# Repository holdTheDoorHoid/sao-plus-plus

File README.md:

# SAO++

Classic Simple Add-Ons, rebuilt for today's badges and for real production runs, plus a growing set of new ones.

The repo holds two kinds of board, kept in separate folders:

- **Ports** (`boards/`): other makers' SAOs, rebuilt to the SAO++ standard with credit to the original maker.
- **SAO++ Originals** (`originals/`): LSOH's own designs, made for SAO++ from scratch.

SAO++ takes older SAOs (the little art boards that plug into conference badges), ports them to the **SAO v1.69bis** 6-pin standard, adds small improvements where they make sense, and publishes them openly. Every board shares the same connector, power switch, battery holder, and LED family, so they can be built side by side on the same reels and the same assembly setup.

## What every SAO++ board has

- **6-pin SAO v1.69bis connector**, surface-mount and shrouded, on the back. Nothing pokes through the art side.
- **SAO / OFF / BATTERY switch**: runs from the badge or from its own CR2032. It is wired so the badge can never charge the coin cell.
- **CR2032 coin cell**: several days of daytime wear on a simple LED board.
- **Boards that need a chip** use a Seeed Studio XIAO ESP32 module instead of a coin cell: the same switch chooses between badge power and the module's own (USB-C or a LiPo).
- **LEDs on the back**: side-firing ones that light the art from the edges, or reverse-mount ones that shine through the board.
- **All parts on the back**; the front is pure art.

The full rules are in [docs/standard.md](docs/standard.md), and the shared parts with live prices are in [docs/parts.md](docs/parts.md).

## Layout

```
boards/<slug>/        one folder per PORT of another maker's SAO
originals/<slug>/     one folder per SAO++ ORIGINAL (LSOH's own design); same layout as a port
  board.yml           provenance, license, permission, features, shared parts used
  README.md           credit to the original maker, what changed, build notes
  hardware/           KiCad 10 project
  art/                source artwork
  production/         Gerbers, drill, BOM and placement files for one board and for a panel
  firmware/           only for boards with a microcontroller
boards/_template/     copy this to start a new board
lib/                  shared KiCad symbols, footprints, 3D models, power block, starter project
docs/                 house standard, approved parts, porting and permission guide
tools/                check_boards.py (paperwork check, runs on every push), gen_footprints.py, saopp_symbols.py,
                      gen_schematic.py, extract_outline.py, saopp_board.py (helpers for each board's build script), panelize.py, export_fab.py
```

## Ports

Other makers' SAOs, rebuilt. Credit and permission status are in each board's README.

| Board | Original maker | Status |
|---|---|---|
| [Fat Pika](boards/fat-pika/) | TwinkleTwinkie (DEF CON 26, 2018) | Designed and rule-checked, not yet built. **Permission pending: not open-licensed**, see the board README |
| [Mad Cat](boards/mad-cat/) | TwinkleTwinkie (DEF CON 26, 2018) | Designed and rule-checked, not yet built. **Permission pending: not open-licensed**, see the board README |
| [Big Green](boards/big-green/) | TwinkleTwinkie (DEF CON 26, 2018) | Designed and rule-checked, not yet built. **Permission pending: not open-licensed**, see the board README |
| [La Bomba](boards/la-bomba/) | TwinkleTwinkie (DEF CON 26, 2018) | Designed and rule-checked, not yet built. **Permission pending: not open-licensed**, see the board README |
| [Nibbler](boards/nibbler/) | TwinkleTwinkie (DEF CON 26, 2018) | Designed and rule-checked, not yet built. **Permission pending: not open-licensed**, see the board README |
| [RBG](boards/rbg/) | lemons4all (DEF CON 26, 2018) | Designed and rule-checked, not yet built. **Permission pending: not open-licensed**, see the board README |
| [Frida](boards/frida/) | lemons4all (DEF CON 26, 2018) | Designed and rule-checked, not yet built. **Permission pending: not open-licensed**, see the board README |
| [Oh My Glob (LSP)](boards/lumpy/) | lemons4all (DEF CON 26, 2018) | Designed and rule-checked, not yet built; the tightest fit of the set (see its README). **Permission pending: not open-licensed** |
| [Hack-Man](boards/hack-man/) | InstantArcade (Bob), 2024 | Recreated from the maker's pictures (no files were published), rule-checked, not yet built. Seeed XIAO ESP32 controller, new Rust firmware. **Permission pending: not open-licensed**, see the board README |
| [Han SAOlo](boards/han-saolo/) | davedarko (2024) | Designed and rule-checked, not yet built. Short life and weak green/blue on a coin cell (calculated). **Permission pending: not open-licensed**, see the board README |
| [Knight Rider (K.I.T.T.)](boards/knight-rider/) | davedarko (2017) | Designed and rule-checked, not yet built. No firmware yet. **Permission pending: not open-licensed**, see the board README |
| [Soot Sprite](boards/soot-sprite/) | davedarko (2026) | Designed and rule-checked, not yet built. **Permission pending: not open-licensed**, see the board README |
| [COVID-19 Test](boards/covid-test/) | davedarko (2022) | Designed and rule-checked, not yet built. **Permission pending: not open-licensed**, see the board README |
| [Penghito Poco](boards/penghito-poco/) | davedarko (year not recorded) | Designed and rule-checked, not yet built. **Permission pending: not open-licensed**, see the board README |
| [Mysterio](boards/mysterio/) | davedarko (2025) | Designed and rule-checked, not yet built. Seeed XIAO ESP32 controller, new Rust firmware (never run on hardware). **Permission pending: not open-licensed**, see the board README |
| [Do Or Donut](boards/do-or-donut/) | davedarko (2019) | Designed and rule-checked, not yet built. Seeed XIAO ESP32 controller, new Rust firmware (never run on hardware). **Four-layer board.** **Permission pending: not open-licensed**, see the board README |
| [Vendetta](boards/vendetta/) | davedarko (2022) | Designed and rule-checked, not yet built. Scaled up 1.23x. **Permission pending: not open-licensed**, see the board README |
| [Hello My Name Is](boards/hello-my-name-is/) | davedarko (2024) | Designed and rule-checked, not yet built. Scaled up 1.1x. **Permission pending: not open-licensed**, see the board README |
| [LECCO postcard](boards/lecco/) | davedarko (2026) | Designed and rule-checked, not yet built. Scaled up 1.2x; badge power only (no cell or switch). **Permission pending: not open-licensed**, see the board README |
| [Sloth](boards/sloth/) | davedarko (2017) | Was a pin; now an SAO. Designed and rule-checked, not yet built. Scaled up 1.3x. No firmware yet. **Permission pending: not open-licensed**, see the board README |
| [Flux Capacitor](boards/flux-capacitor/) | davedarko (2017) | Was a pin; now an SAO. Designed and rule-checked, not yet built. Scaled up 1.35x. No firmware yet. **Permission pending: not open-licensed**, see the board README |
| [Retro Spacehuhn](boards/spacehuhn/) | davedarko (year not recorded) | Was a pin; now an SAO. Designed and rule-checked, not yet built. The chicken logo is Spacehuhn's. **Permission pending: not open-licensed**, see the board README |
| [Mr. Robot](boards/mr-robot/) | davedarko (2019) | Designed and rule-checked, not yet built. Scaled up 1.1x. Seeed XIAO ESP32 controller, new sounder driver, new Rust firmware (never run on hardware). **Permission pending: not open-licensed**, see the board README |

## SAO++ Originals

LSOH's own designs, under the SAO++ licences. None is built yet; the first shortlist of ten
cybersecurity-themed art boards is in [originals/README.md](originals/README.md).

## Adding a board

Read [docs/porting-guide.md](docs/porting-guide.md). In short: confirm the license or get the maker's permission **first**, copy `boards/_template` (into `originals/<slug>/` for an LSOH design, with `permission: own`), start from `lib/template`, and run `python3 tools/check_boards.py`.

## License

- Hardware designs: [CERN-OHL-S-2.0](LICENSE). Anyone can build and sell these; changes you distribute must stay open.
- Artwork: [CC-BY-SA-4.0](LICENSE-ART).
- **These licenses cover SAO++'s own work only**, which includes every board in `originals/` in full. A board marked "permission pending" in its README is not open-licensed: its original design and art stay with the original maker.
- Boards ported from other makers keep their credit, and their original license terms are recorded in each `board.yml`. Where a board's original license differs, its README says so and it takes precedence for that board.

Original designs remain credited to their makers. If you made one of these boards and want it changed or removed, open an issue.

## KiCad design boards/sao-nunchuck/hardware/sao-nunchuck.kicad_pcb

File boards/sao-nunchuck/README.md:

# SAO Nunchuck — SAO++ edition

Originally the **SAO Nunchuck** (hardware V1.0, 2024) by **Andy and Jared Geppert** (ageppert, www.MachineIdeas.com): https://github.com/ageppert/SAO_Nunchuck (project page: https://hackaday.io/project/198000-sao-nunchuck)

**License:** the original is MIT-licensed, "Copyright (c) 2024 Andrew Geppert" ([original/LICENSE.md](original/LICENSE.md)). The license sits at the top of the maker's repository and no file inside carries a different notice, so it covers the board design as well as the demo code. That notice must stay with any copy.

> **The names and shapes are Nintendo's.** "Wii" and "Nunchuk" are Nintendo trademarks. The board says "SAO NUNCHUCK" on the back (the maker's spelling) and shows the outline of a Wii Remote and a Nunchuk controller on the front, joined by a chain like a pair of nunchaku. There is no Nintendo logo on it. The maker's MIT license covers his drawing; it cannot give anyone rights in Nintendo's names or product shapes. If boards are sold, describe them as "for use with" the controller, never as a Nintendo product. The owner should decide whether that is enough (see "Decisions for the owner").

## What the original actually is

Read from the maker's files (the survey guessed "pass-through, hardly any art"; the first half is right, the second is not):

- **A plug-in adaptor with no parts that do anything.** A Nunchuck controller talks I2C (the same two-wire bus an SAO port has) and runs on 3.3 V. The board joins the badge's 3.3 V, ground, SDA and SCL straight to the controller's plug. No chip, no LED, no resistor, no pull-ups. The badge's own program reads the joystick, two buttons and tilt sensor at I2C address 0x52 (printed on the back).
- **The board is the socket.** There is no bought connector for the controller. The top edge has a notch with a 6.3 mm wide tongue in it, carrying five gold fingers (three on the back, two on the front). The controller's plug slides over the tongue; the notch is shaped to take the plug's body and latches. One of the six plug contacts ("device detect") lands on a finger that is not connected to anything; the sixth has no finger.
- **Two Qwiic sockets** (small 4-pin JST SH connectors, the SparkFun / Adafruit plug-and-play I2C standard) on the back near the top corners, wired to the same four lines, so the board can also join a Nunchuck to a Qwiic gadget, or chain other I2C boards off the badge.
- **The SAO header** was a through-hole 2×3 at the bottom, with six extra gold fingers on the bottom edge so a right-angle socket could be soldered on instead (that is what the maker's photo shows).
- **It does have art:** a Wii Remote and a Nunchuck as a pair of nunchaku, in bare gold copper on a black board, 38.1 × 50.8 mm.
- **Demo code** (`original/Firmware/`, Arduino, for an RP2040 board) shows how to read the controller. It is the badge's job, not the add-on's: there is nothing on this board to program.

## What SAO++ makes of it

The same adaptor, with the house connector on the back. **One part to buy and place.**

| | Original (V1.0) | SAO++ rev A |
|---|---|---|
| SAO connector | Through-hole 2×3 at the bottom (six holes through the front), plus six edge fingers | 6-pin SAO v1.69bis shrouded, keyed SMD connector on the back, in the same three columns, key slot up. Nothing shows on the front |
| Power | Badge 3.3 V only | **Badge 3.3 V only** (no coin cell, no switch: see below). "BADGE POWER ONLY" is printed on the back |
| Nunchuck plug | Five gold fingers on a tongue in the top notch | **Unchanged**: same notch, same tongue, same fingers, same wiring |
| Qwiic sockets | Two JST SH 4-pin sockets fitted | **Pads only, not fitted.** The pads and wiring are all there; solder a socket on by hand if you want one |
| Front art | — | Unchanged, apart from the old header's six holes and three bottom fingers, which are gone |
| Back | — | Title, I2C address, makers' credit and logo, "2024" and "V1.0" untouched. "Manufactured by PCBX.COM" removed (it would not be true of these boards). Added: "SAO++ rA   BADGE POWER ONLY", a pin-1 mark, and a ground copper fill under the mask |

**How to use it:** plug the board into a badge's SAO port, then push a Nunchuck plug onto the tongue at the top until it clicks. The badge needs a program that reads a Nunchuck (libraries are linked in the maker's README).

## Why there is no coin cell and no switch (a recorded exception to the house standard)

Every other SAO++ board so far has the CR2032 clip and the SAO / OFF / BAT switch. This one does not, on purpose:

- **Nothing on it lights up or runs on its own.** A Nunchuck with nobody reading it does nothing, and the only thing that can read it is the badge. A cell would power a controller that is not being listened to.
- **A cell here would be the risky case in the standard.** Section 3 warns that when the badge's I2C lines are connected to something powered by the cell, a little current can leak from the badge into the cell. This board is *only* I2C lines. Fitting a cell would mean adding the protective diode as well, three parts in all, to guard a feature nobody can use.
- **It keeps the board to one shared part.**

So SAO pin 1 (3.3 V) goes straight to the plug and the Qwiic pads, as the maker drew it, instead of through a switch (the standard's pin-1 rule assumes a switch exists). With no cell on the board there is nothing to back-feed.

## Other compromises, each one deliberate

- **Two gold fingers are on the front.** The house rule is "front = art only". A Nunchuck plug has contacts on both faces of the tongue, so two fingers must be on the front. They are the maker's and are part of the look.
- **The maker's tracks on the front stay.** Five thin tracks cross the front just above the chain (under the mask, faintly visible) with 16 small vias. They are his way of getting four lines to both Qwiic positions. They were left exactly as drawn rather than re-routed.
- **Connector at the bottom, not the middle.** The standard prefers the connector near the board's centre of weight. The middle of the back is the maker's title and credit, and the original header was at the bottom too. The connector's pads end 3.4 mm inside the bottom edge (rule: 3 mm). The controller's cable will pull on the top of the board while the connector holds the bottom: see the checklist.
- **Qwiic sockets not fitted.** The JST SH socket is not on the shared parts list, and fitting it would add a reel that only this board uses. The pads cost nothing. The maker's files name the part as JST **SM04B-SRSS-TB** (his file also carries LCSC C160404 and a Digi-Key number; none of these was re-checked here).
- **"V1.0" and "2024" stay** on the back as the maker's version of the design, next to the new "SAO++ rA".
- **The title is slightly wider than the board.** The maker's "SAO NUNCHUCK" lettering runs 0.2–0.4 mm past both side edges, so the tips of the S and K are trimmed, exactly as on his boards. Left alone.
- **Ground copper fill on the back** is new (the standard asks for copper round the connector to stiffen the joint). It stops 0.55 mm from the edge and stays off the tongue and out of the notch.

## Things to check on the first prototype

1. **Plug fit.** Push a real Nunchuck plug on. It should slide over the tongue, click, and not wobble. The tongue, notch and fingers are the maker's, unchanged, and he built and used his, but **the board must be 1.6 mm thick** for the plug's springs to grip.
2. **Does it work.** On a badge with a Nunchuck program (or the maker's Arduino demo on an RP2040 board), check the joystick and buttons read correctly. Check with a genuine controller and, if you have one, a clone: some clones need pull-up resistors that genuine ones have built in, and this board, like the original, has none (the badge is expected to provide them).
3. **Pin 1 position.** The connector keeps 3.3 V in the same corner as every other SAO++ board. Confirm against a v1.69bis badge before a production run. A wrong guess here would put 3.3 V and ground the wrong way round on the controller.
4. **Current.** Measure what the controller draws from the badge. It was not measured here; the house budget is 50 mA.
5. **Cable pull.** With the controller plugged in and hanging or being used, check the SMD connector's solder joints are not being levered. If they are, the fix is the connector higher up the board, which means moving the maker's credit block (owner's call).
6. **Clearance behind the board.** The plug's body is thicker than the board and sticks out behind it at the top. The SAO connector holds the board about 9 mm off the badge, which should be enough; check on a real badge.
7. **Gold finger wear.** ENIG gold is thin. It is fine for occasional plugging; if a board is going to be plugged hundreds of times, ask the fab about hard gold.

## Files

- `hardware/sao-nunchuck.kicad_pro` — KiCad 10 project (schematic + board). ERC: 0 issues. DRC: 0 errors, 0 unconnected, schematic matches board. 2 warnings remain: the maker's logo library is not installed (the logo itself is in the board), and the maker's title lettering touches the board edge (see above).
- `hardware/circuit.json` — the circuit as data; `tools/gen_schematic.py sao-nunchuck` and `hardware/build_board.py` both read it. `hardware/fix_schematic.py` then marks the fingers and the Qwiic pads "not in BOM".
- `hardware/build_board.py` — rebuilds the board from `original/` plus the SAO++ changes; every decision is in there with a comment. It also re-applies the project's rule settings (the maker's 6 mil spacing between his tracks and vias is kept as the board's minimum).
- `hardware/sao-nunchuck.kicad_dru` — one extra rule: the plug fingers may run to within 0.1 mm of the tongue's tip (the maker's are 0.14 and 0.19 mm).
- `hardware/parts_local.py`, `hardware/sao-nunchuck-local.pretty/`, `hardware/make_local_footprints.py` — the two footprints kept from the maker (plug fingers; Qwiic pads), lifted out of his board file.
- `hardware/outline.json` — the maker's outline as one polygon.
- `production/` — everything a board house needs, for one board (`single/`) and a 2×2 panel (`panel/`). Start with [production/README.md](production/README.md).
- `original/` — the maker's KiCad 8 project, schematic PDF, Gerbers, SVG art, Arduino demo, README and LICENSE (commit 6b02ca0). Left out: his two photos (see his repository) and KiCad's 3.5 MB footprint cache file.

## Parts cost (parts only)

| Part | Qty | Each |
|---|---|---|
| Connector XFCN BH254VS-6P (LCSC C492445) | 1 | $0.10 @340 (docs/parts.md, checked 2026-11-10) |
| **Total** | | **about $0.10** |

Not included: the bare board (38.1 × 50.8 mm, ENIG), assembly, and the controller. Optional Qwiic sockets are not priced: no price was checked.

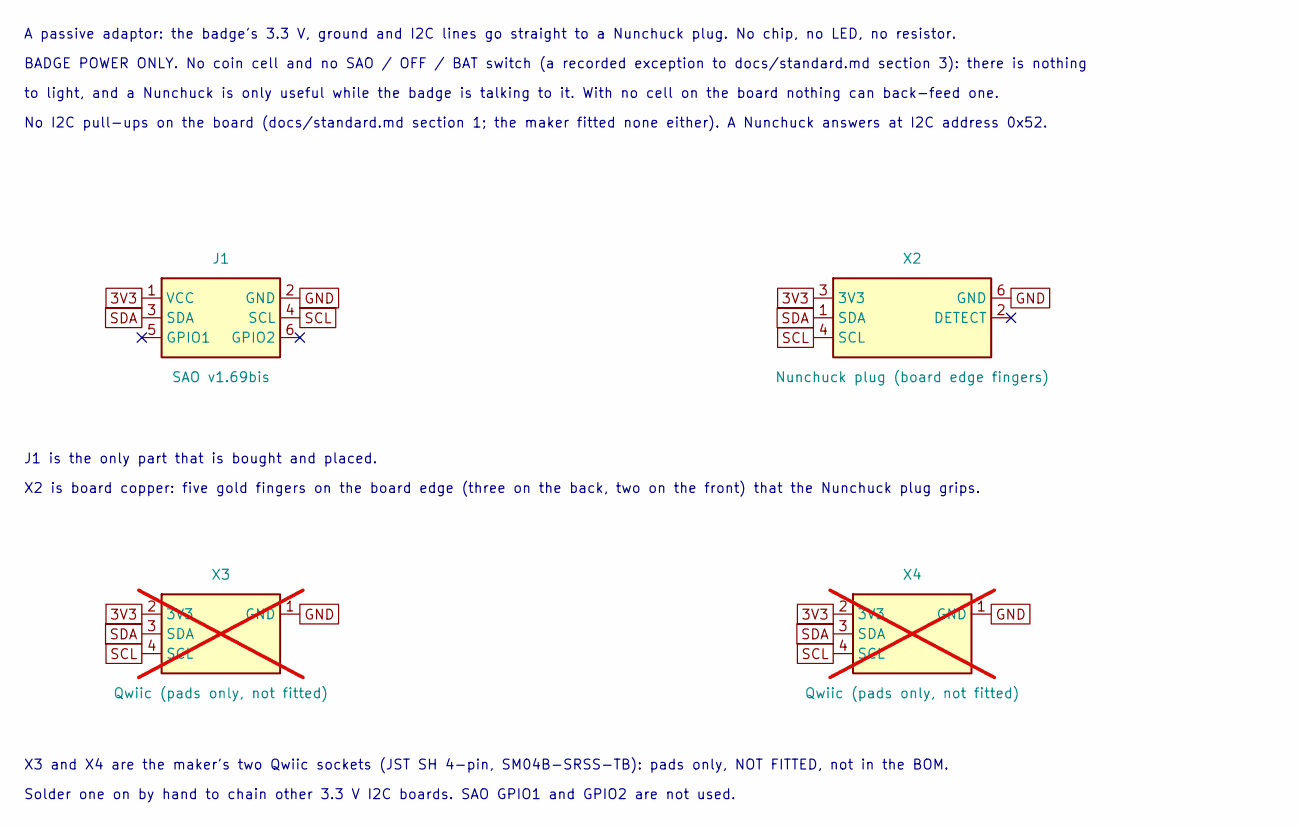
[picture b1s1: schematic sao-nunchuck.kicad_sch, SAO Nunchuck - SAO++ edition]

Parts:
J1: SAO v1.69bis; SAOPP_CONN-01_BoxHeader_2x03_P2.54mm_SMD_XFCN_BH254VS-6P; MPN BH254VS-6P; LCSC C492445
X2: Nunchuck plug (board edge fingers); Nunchuck_Plug_EdgeFingers; MPN none: PCB copper, nothing fitted
X3, X4: Qwiic (pads only, not fitted); Qwiic_JST_SH_SM04B-SRSS-TB_NotFitted; MPN SM04B-SRSS-TB; LCSC C160404; not fitted

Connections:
3V3: J1.1 (VCC), X2.3 (3V3), X3.2 (3V3), X4.2 (3V3)
GND: J1.2 (GND), X2.6 (GND), X3.1 (GND), X4.1 (GND)
SCL: J1.4 (SCL), X2.4 (SCL), X3.4 (SCL), X4.4 (SCL)
SDA: J1.3 (SDA), X2.1 (SDA), X3.3 (SDA), X4.3 (SDA)

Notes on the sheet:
A passive adaptor: the badge's 3.3 V, ground and I2C lines go straight to a Nunchuck plug. No chip, no LED, no resistor.
BADGE POWER ONLY. No coin cell and no SAO / OFF / BAT switch (a recorded exception to docs/standard.md section 3): there is nothing
to light, and a Nunchuck is only useful while the badge is talking to it. With no cell on the board nothing can back-feed one.
No I2C pull-ups on the board (docs/standard.md section 1; the maker fitted none either). A Nunchuck answers at I2C address 0x52.
J1 is the only part that is bought and placed.
X2 is board copper: five gold fingers on the board edge (three on the back, two on the front) that the Nunchuck plug grips.
X3 and X4 are the maker's two Qwiic sockets (JST SH 4-pin, SM04B-SRSS-TB): pads only, NOT FITTED, not in the BOM.
Solder one on by hand to chain other 3.3 V I2C boards. SAO GPIO1 and GPIO2 are not used.

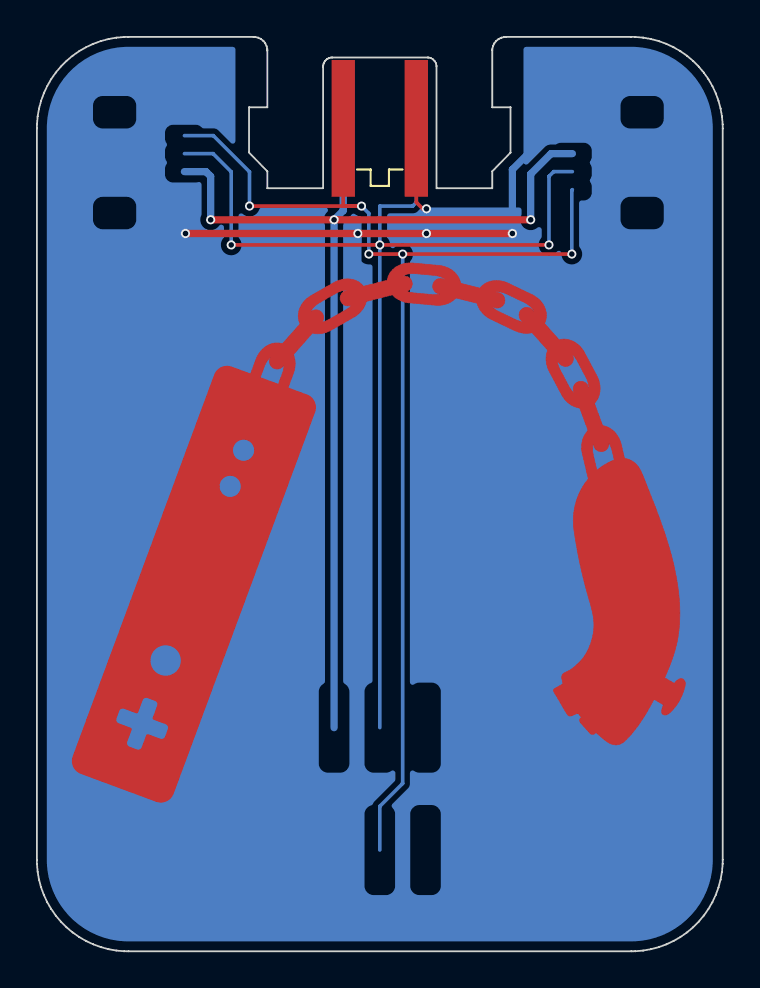
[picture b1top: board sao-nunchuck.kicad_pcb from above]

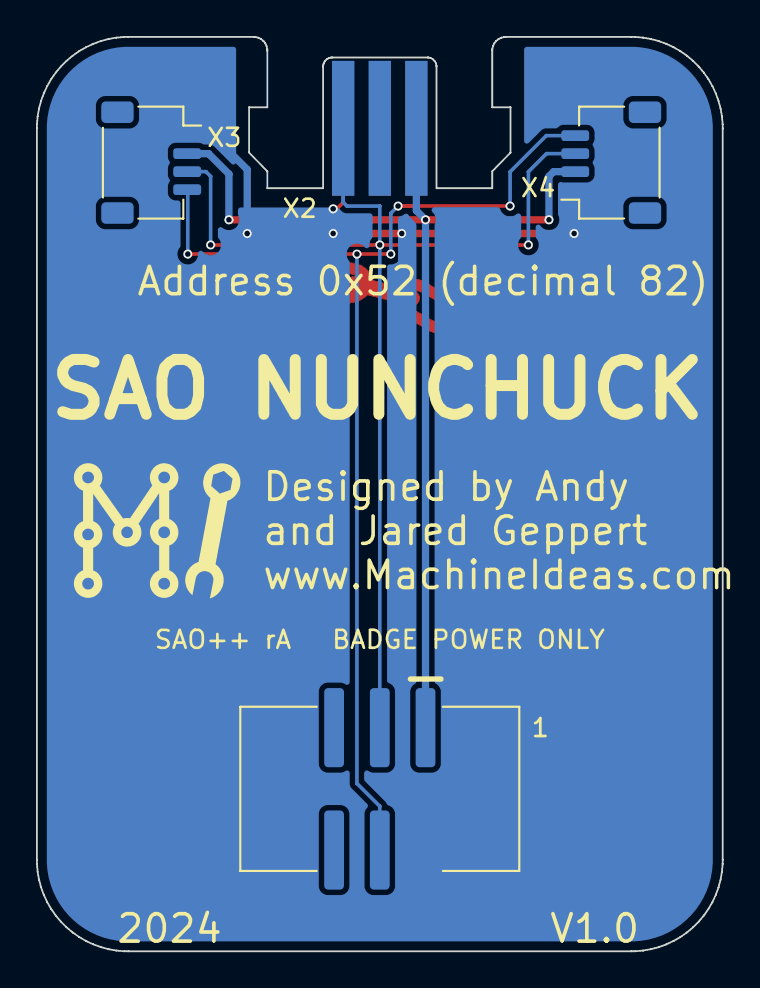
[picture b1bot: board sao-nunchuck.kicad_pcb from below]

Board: 2 copper layers, 38.1 x 50.8 mm, 5 parts (4 on the bottom side), 4 nets.

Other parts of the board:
L1: Machine_Ideas_logo

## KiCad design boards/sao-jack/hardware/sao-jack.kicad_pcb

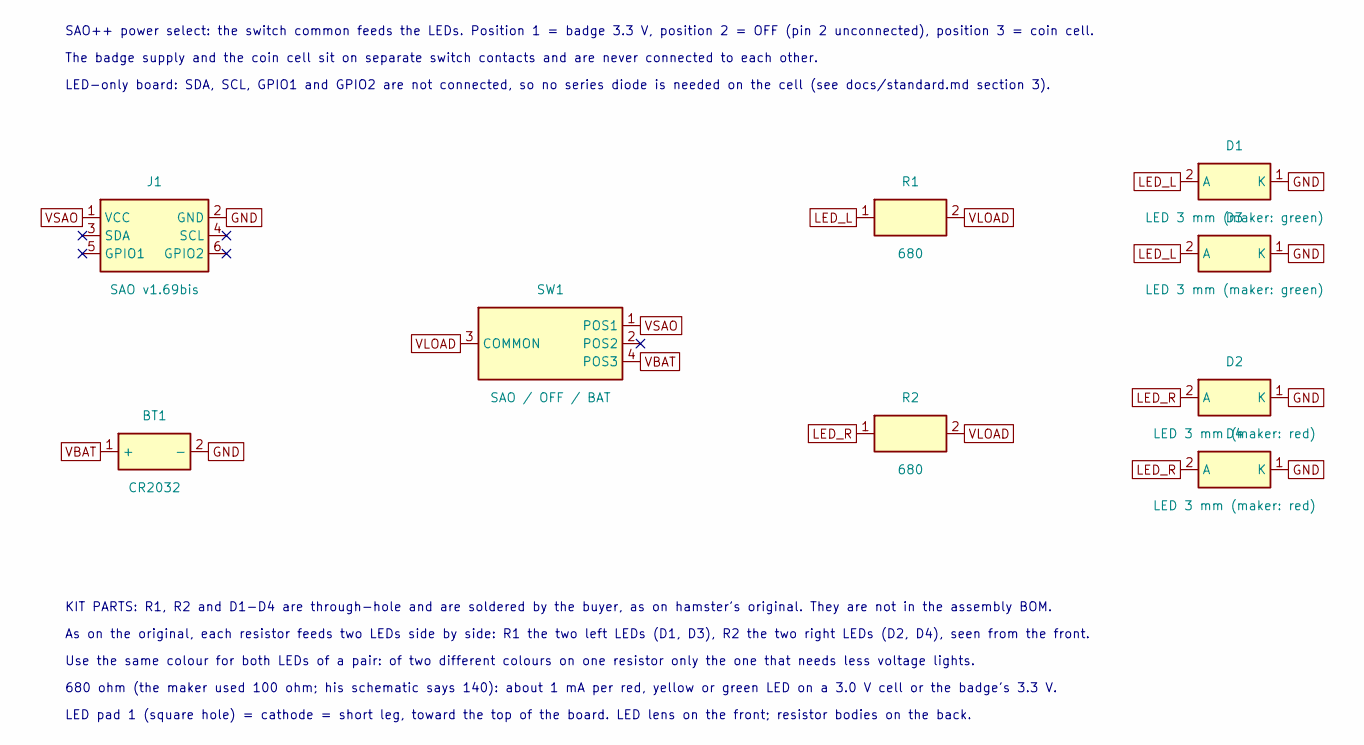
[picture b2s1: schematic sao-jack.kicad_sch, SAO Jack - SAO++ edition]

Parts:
BT1: CR2032; SAOPP_BAT-01_CR2032_SMD_TE_BAT-HLD-001; MPN BAT-HLD-001; LCSC C7501066
D1, D3: LED 3 mm (maker: green); LED_D3.0mm; MPN kit part, not chosen: any 3 mm (T-1) LE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
D2, D4: LED 3 mm (maker: red); LED_D3.0mm; MPN kit part, not chosen: any 3 mm (T-1) LE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
J1: SAO v1.69bis; SAOPP_CONN-01_BoxHeader_2x03_P2.54mm_SMD_XFCN_BH254VS-6P; MPN BH254VS-6P; LCSC C492445
R1, R2: 680; R_Axial_DIN0204_L3.6mm_D1.6mm_P7.62mm_Horizontal; MPN kit part, not chosen: any 680 ohm 1/8 W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
SW1: SAO / OFF / BAT; SAOPP_SW-01_Slide_SP3T_CK_PCM13SMTR; MPN PCM13SMTR; LCSC C221842

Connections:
GND: BT1.2 (-), D1.1 (K), D2.1 (K), D3.1 (K), D4.1 (K), J1.2 (GND)
LED_L: D1.2 (A), D3.2 (A), R1.1
LED_R: D2.2 (A), D4.2 (A), R2.1
VBAT: BT1.1 (+), SW1.4 (POS3)
VLOAD: R1.2, R2.2, SW1.3 (COMMON)
VSAO: J1.1 (VCC), SW1.1 (POS1)

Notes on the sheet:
SAO++ power select: the switch common feeds the LEDs. Position 1 = badge 3.3 V, position 2 = OFF (pin 2 unconnected), position 3 = coin cell.
The badge supply and the coin cell sit on separate switch contacts and are never connected to each other.
LED-only board: SDA, SCL, GPIO1 and GPIO2 are not connected, so no series diode is needed on the cell (see docs/standard.md section 3).
KIT PARTS: R1, R2 and D1-D4 are through-hole and are soldered by the buyer, as on hamster's original. They are not in the assembly BOM.
As on the original, each resistor feeds two LEDs side by side: R1 the two left LEDs (D1, D3), R2 the two right LEDs (D2, D4), seen from the front.
Use the same colour for both LEDs of a pair: of two different colours on one resistor only the one that needs less voltage lights.
680 ohm (the maker used 100 ohm; his schematic says 140): about 1 mA per red, yellow or green LED on a 3.0 V cell or the badge's 3.3 V.
LED pad 1 (square hole) = cathode = short leg, toward the top of the board. LED lens on the front; resistor bodies on the back.

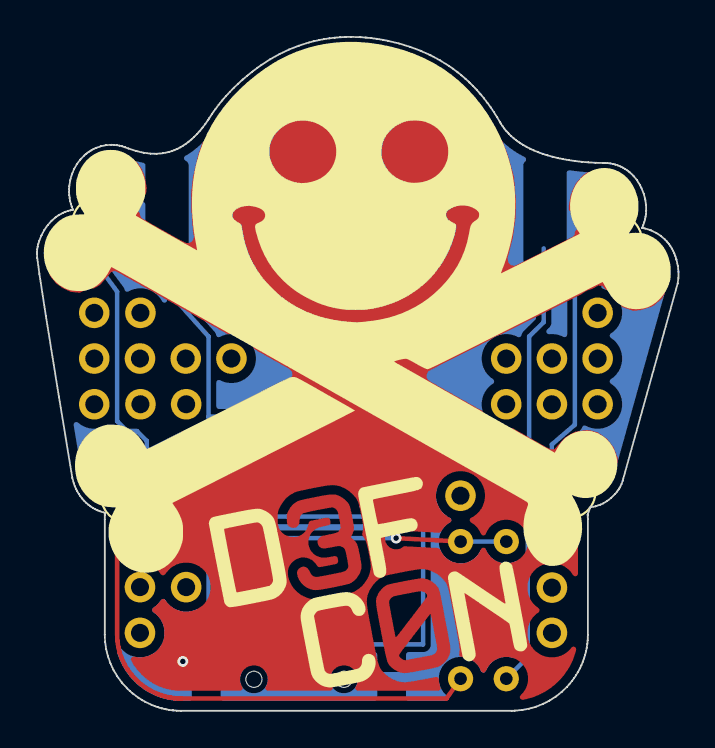
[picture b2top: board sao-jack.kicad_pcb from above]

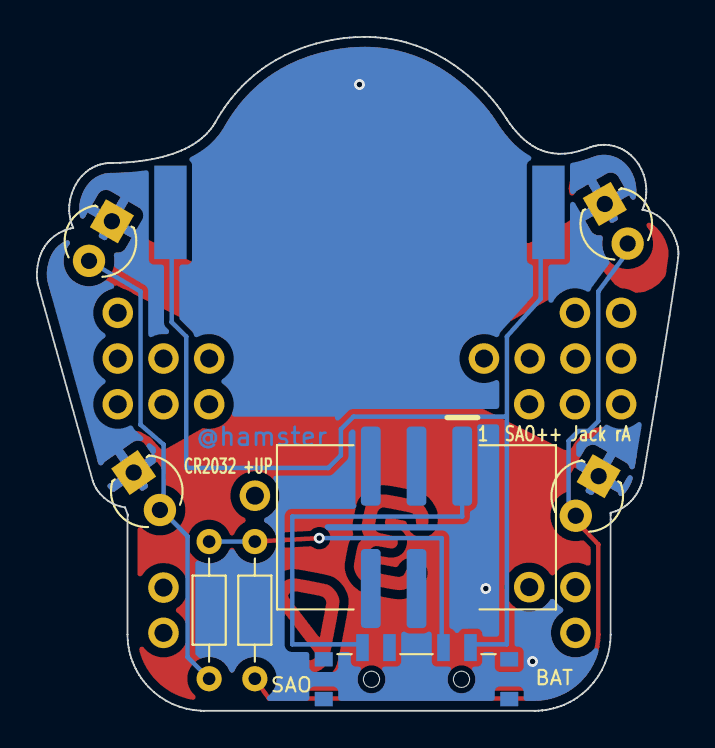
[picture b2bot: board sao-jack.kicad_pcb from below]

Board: 2 copper layers, 35.6 x 37.4 mm, 9 parts (5 on the bottom side), 6 nets.

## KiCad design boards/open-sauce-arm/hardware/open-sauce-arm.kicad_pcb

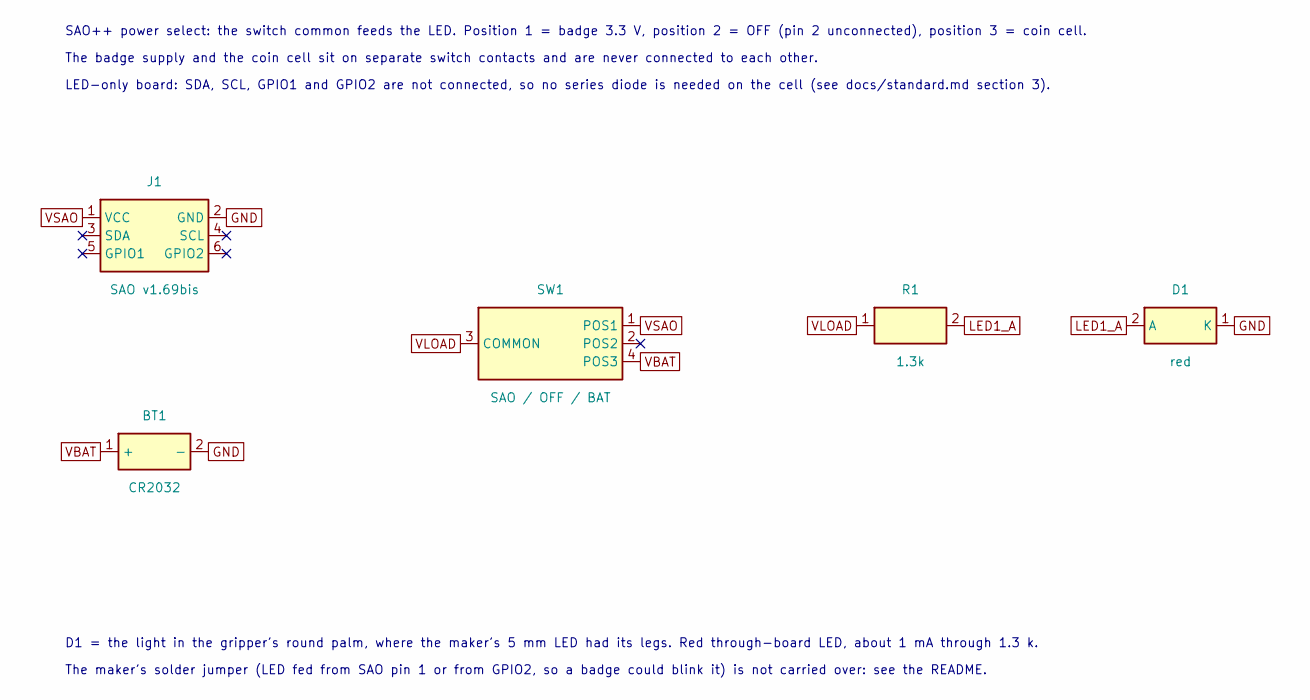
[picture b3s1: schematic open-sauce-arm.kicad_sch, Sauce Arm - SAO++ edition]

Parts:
BT1: CR2032; SAOPP_BAT-01_CR2032_SMD_TE_BAT-HLD-001; MPN BAT-HLD-001; LCSC C7501066
D1: red; SAOPP_LED-10_1206_ReverseMount_ThroughBoard; MPN LTST-C230KRKT; LCSC C125107
J1: SAO v1.69bis; SAOPP_CONN-01_BoxHeader_2x03_P2.54mm_SMD_XFCN_BH254VS-6P; MPN BH254VS-6P; LCSC C492445
R1: 1.3k; SAOPP_R_0603_1608Metric; MPN 0603WAF1301T5E; LCSC C22767
SW1: SAO / OFF / BAT; SAOPP_SW-01_Slide_SP3T_CK_PCM13SMTR; MPN PCM13SMTR; LCSC C221842

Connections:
GND: BT1.2 (-), D1.1 (K), J1.2 (GND)
LED1_A: D1.2 (A), R1.2
VBAT: BT1.1 (+), SW1.4 (POS3)
VLOAD: R1.1, SW1.3 (COMMON)
VSAO: J1.1 (VCC), SW1.1 (POS1)

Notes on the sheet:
SAO++ power select: the switch common feeds the LED. Position 1 = badge 3.3 V, position 2 = OFF (pin 2 unconnected), position 3 = coin cell.
The badge supply and the coin cell sit on separate switch contacts and are never connected to each other.
LED-only board: SDA, SCL, GPIO1 and GPIO2 are not connected, so no series diode is needed on the cell (see docs/standard.md section 3).
D1 = the light in the gripper's round palm, where the maker's 5 mm LED had its legs. Red through-board LED, about 1 mA through 1.3 k.
The maker's solder jumper (LED fed from SAO pin 1 or from GPIO2, so a badge could blink it) is not carried over: see the README.

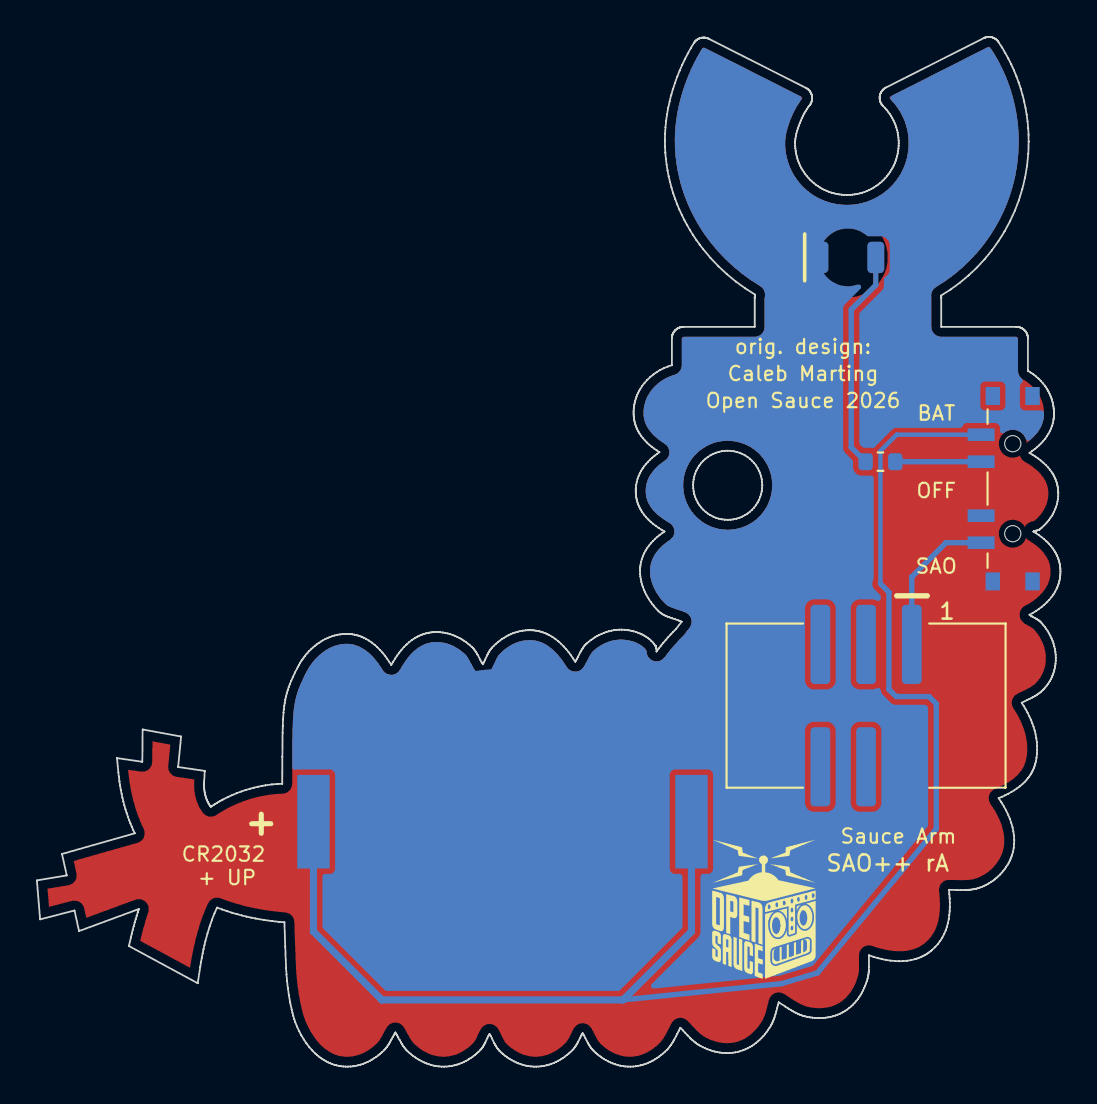
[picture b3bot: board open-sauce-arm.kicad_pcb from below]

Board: 2 copper layers, 56.9 x 57.2 mm, 5 parts (5 on the bottom side), 5 nets.

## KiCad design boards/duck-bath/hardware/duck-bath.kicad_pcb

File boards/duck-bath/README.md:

# Duck Bath — SAO++ edition

Originally **duckBATH**, one of the two **duckGLOW** add-ons by **Adrian Studer (astuder)**, 2024: https://github.com/astuder/duckglow (project page: https://hackaday.io/project/198918-duckglow-sao).

> **Licence: open.** The maker's repository carries the MIT licence and the CERN Open Hardware Licence v2 Permissive in one file ([original/LICENSE.md](original/LICENSE.md)), © 2024 Adrian Studer, and his schematic sheet is marked CERN-OHL-P. Both allow changing, making and selling with credit. His files, as downloaded (commit `f58ce25`), are in [original/](original/); the notice is kept there, in this README and on the back of the board.

*(The pictures use KiCad's default green. The maker's own boards are **white with black lines**: see the ordering notes.)*

A bathtub full of foam with a real toy rubber duck sitting in it. A light inside the duck makes it glow, slowly breathing yellow. A badge can change the colour and the breathing over I2C.

## What the original really is

- A 40 × 20 mm two-layer board. The front is only a drawing (silkscreen lines over a plain copper plate).
- **One ordinary 5 mm RGB LED standing up on the front**, in the foam. A small hollow rubber duck is pushed over it. That LED is the only light.
- A WCH CH32V003 chip that dims the LED's three colours, a small boost converter so it runs from 0.9 to 5 V, a transistor against reversed power, two I2C pull-up resistors, and two solder jumpers that change the I2C address.
- It answers on I2C (address 0x6C) with a table of settings: brightest and dimmest value, fading speed and starting point for each colour. It can also be driven like one addressable LED through the GPIO2 pin, and it can store settings.
- **Shared design:** the maker's other board, duckJAWS, has the same circuit and the same firmware with a different outline, different art and extra red lights behind the picture. Only duckBATH is ported here.

The survey called it "CH32V003 + RGB", which is right; it did not say that the light is a through-hole LED on the art side with a toy duck over it, which is the hard part for this project.

## Why the board is bigger

**Everything is enlarged 1.6 times: 64.1 × 32.0 mm instead of 40.0 × 20.0 mm.** The outline and the art grow together; the parts keep their real size.

The XIAO module is 21 × 17.8 mm and its USB socket has to stick out over an edge. On this shape the only edge that works is the bottom, between the two feet: at the side walls the rim of the tub sticks out further than the socket would, and a plug would hit it. Standing upright under the foam, the module needs most of the tub's height.

- Below about 1.4 the module does not fit between the foam and the bottom edge with its plug clear of the foot (checked against the outline by a script).
- At 1.4 to 1.5 the parts fit only edge to edge, and at 1.5 just 2 mm is left between the duck hole and the module, where five tracks have to pass. This was worked out from the part sizes; no board was drawn at those sizes.
- 1.6 is the size that was drawn and routed: every part has its own space and the tracks fit. Factors between 1.5 and 1.6 were not tried.

The duck does not grow: it is a bought toy. It will look smaller against the tub than on the maker's board unless a bigger duck is used.

## What changed from the original

| | Original (v0.2) | SAO++ rev A |
|---|---|---|
| Size | 40.0 × 20.0 mm | 64.1 × 32.0 mm (1.6×) |
| Light | One 5 mm RGB LED standing on the front, inside the duck | **A 5 mm hole** where that LED stood, and **two small RGB LEDs on the back** at the hole's edge (one to the left, one below), lying on their sides and shining into the hole. The duck sits over the hole. Both LEDs always show the same colour |
| Controller | CH32V003 | **Seeed Studio XIAO ESP32** module soldered flat on the back: C3, S3 or C6 all fit the same pads. USB-C at the bottom edge, between the feet |
| Power | Badge only, 0.9–5 V through a boost converter | Slide switch on the left wall: **SAO** (badge power) / **OFF** / **USB-BAT** (USB-C, or a LiPo cell on the new JST-PH connector at the bottom edge, which the XIAO charges). The boost converter and the reverse-power transistor are gone: the board now needs the badge's normal 3.3 V |
| Connector | 6-pin SMD pin header | 6-pin SAO v1.69bis, surface-mount, shrouded and keyed, 3.3 mm left of the duck's centre line |
| I2C address | 0x6C, or 0x6D–0x6F with two solder jumpers | 0x6C only. The jumpers are not on the board; the address is one line in the firmware |
| I2C pull-ups | Two 10 kΩ on the add-on | None (the house rule: the badge provides them) |
| Front | Silkscreen art over a copper plate; the LED's four pads and sixteen small holes (vias) show | The same art, scaled, over a copper plate. The duck hole, the switch's two 0.9 mm peg holes at the left wall, eight covered 0.3 mm vias, and **two short tracks under the solder mask**: 6.6 mm in the middle of the tub and 3.5 mm near the left wall. On a white board they should be all but invisible |
| Back text | "duckBATH", version, I2C address, pin notes | Board name, "orig: duckBATH v0.2 (c) 2024 Adrian Studer, CERN-OHL-P, astuder/duckglow", switch and battery labels, the USB warning |

**No new part types.** Everything is already on the shared list: connector, switch, XIAO, LiPo connector, the RGB LED, the 330 Ω resistor and the 100 nF capacitor.

### Why two tracks are on the front

All other chip boards so far keep every track on the back. Here the XIAO's pins and the SAO connector's pins are in opposite orders (the XIAO has SCL above SDA, the connector wants them the other way round), and the switch's three contacts are in the opposite order to the three lines that reach it. On one layer two lines would have to cross. Each crossing is a short hop on the front, under the mask, through two covered vias. Every attempt to avoid them needed something worse (a track between the pads of the module for the whole supply, or a much bigger board).

## The duck and the light: read this before building

This is the part of the port with the least backing.

- On the original the LED is **inside** the duck. Here the two LEDs are **behind the board**, at the rim of a 5 mm hole, and shine across it. Only part of their light turns the corner and goes forward through the hole into the duck.
- Expect to need a **light guide in the hole**: a blob of clear hot glue filling the hole and the duck's opening (the Hack-Man maker did exactly this with the same LEDs), or a short piece of 5 mm clear plastic rod pushed through the hole into the duck. Neither has been tried.
- The duck is glued on the front over the hole. The maker's duck was held by the LED it was pushed onto; here nothing holds it but glue.
- Each LED gives at most 5 mA per colour, 30 mA for both at full white, roughly what the maker's single LED drew through its 100 Ω resistors (an estimate, not a measurement). Through a hole from behind it will be dimmer than an LED inside the duck.

If the first prototype is too dim, the fall-back is the maker's own way: a 5 mm through-hole RGB LED soldered on the front in place of the hole. That part is not on the shared list and breaks the "nothing on the front" rule, so it is a decision for the owner (see "Decisions").

## How the power switch works here

| Knob | Badge 3.3 V | What runs the board |
|---|---|---|
| **SAO** (lowest, seen from the front) | connected to the XIAO's 3V3 pin and the LEDs | the badge |
| **OFF** (middle) | disconnected | nothing from the badge. If USB or a LiPo is attached the XIAO still has power, so the switch tells it to blank the LEDs and sleep |
| **USB-BAT** (highest) | disconnected | the XIAO's own regulator, from USB-C or the LiPo |

- **OFF is a sleep, not a hard cut, when a LiPo is attached.** Unplug the cell for storage.
- **Do not plug in USB while the knob is on SAO and the board is on a badge.** Two 3.3 V regulators would be joined. It is printed on the back.
- **The original ran from 0.9 to 5 V; this one needs 3.3 V.** A badge that feeds its add-ons straight from two AA cells will not run it.
- **No coin cell on this board.**

## Things to check on the first prototype

1. **Light in the duck** (above). The first thing to look at.
2. **Firmware.** It has **never been compiled**, let alone run: see [firmware/README.md](firmware/README.md).
3. **Badge power into the XIAO's 3V3 pin**, on each module type you plan to use, as on Hack-Man.
4. **USB plug.** The module's end sits 0.5 mm inside the bottom edge at the middle of the socket, so the socket sticks out 1.0 mm (Hack-Man: 1.5 mm). A 12.6 mm wide plug body ends level with the notch beside the right foot, and the foot itself is about 1.5 mm further out at that height. Check a real cable seats fully. One corner of the module hangs 0.3 mm over the small notch between the tub and the right foot; it has no pad there.
5. **LED land pattern** (the shared footprint's body position is an estimate) and that both lenses point into the hole. D1 is below the hole, D2 to its left (seen from the front).
6. **LiPo polarity**: + is the pad nearer the middle of the board, marked on the back. Check the cell with a meter. There is no protection.
7. **Battery pads need reflow**: they are under the module, as on the other XIAO boards.
8. **Switch labels**: if SAO and USB/BAT turn out swapped the silkscreen is wrong, not the wiring. The knob comes out of the left wall, which bends by 0.3 mm along the switch; the knob stands 0.8 mm proud in the middle.
9. **Pin 1 position** against a known v1.69bis badge.
10. **Height** of the module and a plugged LiPo lead behind the board.
11. **The two front tracks**: that they do not show through the mask colour you order.

## Pin map

| XIAO pin | Goes to |
|---|---|
| D10 | LED data, through 330 Ω. LED 1 is below the hole, LED 2 to its left |
| D4 / D5 | SAO SDA / SCL |
| D7 / D6 | SAO GPIO1 / GPIO2, each through 330 Ω (not used by the firmware) |
| D1 | High when the switch is on OFF |
| 3V3, GND | the board's 3.3 V rail and ground |
| BAT+ / BAT− (under the module) | the JST-PH LiPo connector |
| D0, D2, D3, D8, D9, 5V | not connected |

## Decisions for the owner

1. **Light: hole and two LEDs from behind (as drawn), or the maker's 5 mm LED on the front?** Recommendation: build rev A as drawn and try it with hot glue in the hole. Go to the front LED only if that is too dim.
2. **Front tracks:** accept two short tracks under the mask on the art side? Recommendation: yes on a white board. The alternative is a bigger board again.
3. **I2C address jumpers:** the maker's board could be set to four addresses; this one has one. Recommendation: leave it; add one jumper on spare pin D3 only if someone wants two ducks on one badge.
4. **Board colour:** white mask with black print, like the maker's? Recommendation: yes.
5. **Scale 1.6** (64 × 32 mm): accept, or ask for a try at 1.55? Recommendation: accept.

## Files

- `hardware/duck-bath.kicad_pro`: KiCad 10 project (schematic + board). ERC: 0. DRC: 0 errors, 0 unconnected, schematic matches the board; 1 warning, a "copper sliver" in the back ground copper where it squeezes between tracks (KiCad gives no position for it; harmless).
- `hardware/circuit.json`: the circuit as data; `tools/gen_schematic.py duck-bath` and the build script both read it.
- `hardware/build_board.py`: builds the board from the maker's file in `original/` and `circuit.json`; every placement and track is in there with a comment. `labels.json` holds the back lettering, `severities.json` the rule settings it re-applies to the project file.
- `hardware/duck-bath.kicad_dru`: no extra rules (the art is silkscreen, so nothing needs an exception).
- `original/`: the maker's board, schematic, footprints, drawing and licence, unchanged. His firmware and photos are not copied: see his repository.
- `firmware/`: new Rust firmware. **Never compiled.** No licence chosen for it yet, as for Hack-Man.
- `production/`: files for a board house, one board (`single/`) and a 2×2 panel (`panel/`). Start with [production/README.md](production/README.md).

## Parts cost (parts only, LCSC list prices from docs/parts.md, checked 2026-11-10)

| Part | Qty | Each @ ~100 boards |
|---|---|---|
| Connector XFCN BH254VS-6P (LCSC C492445) | 1 | $0.10 |
| Switch C&K PCM13SMTR (Digikey) | 1 | ~$0.90 |
| RGB LED OPSCO SK6805-EC3210R (LCSC C5378735) | 2 | $0.068 |
| LiPo connector JST S2B-PH-SM4-TB (LCSC C295747) | 1 | $0.16 |
| Capacitor 100 nF 0603 (LCSC C14663) | 1 | <$0.01 |
| Resistor 330 Ω 0603 (LCSC C23138) | 3 | <$0.01 |
| **Total without the module and the duck** | | **about $1.30** |
| Seeed Studio XIAO ESP32-C3 / S3 / C6 | 1 | not priced here |
| Toy rubber duck, hollow soft vinyl, about 40 mm wide judging by the maker's photo | 1 | not priced here, and not sourced: the maker's project page was not read for which duck he used |

The bare board and the optional LiPo cell are not included.

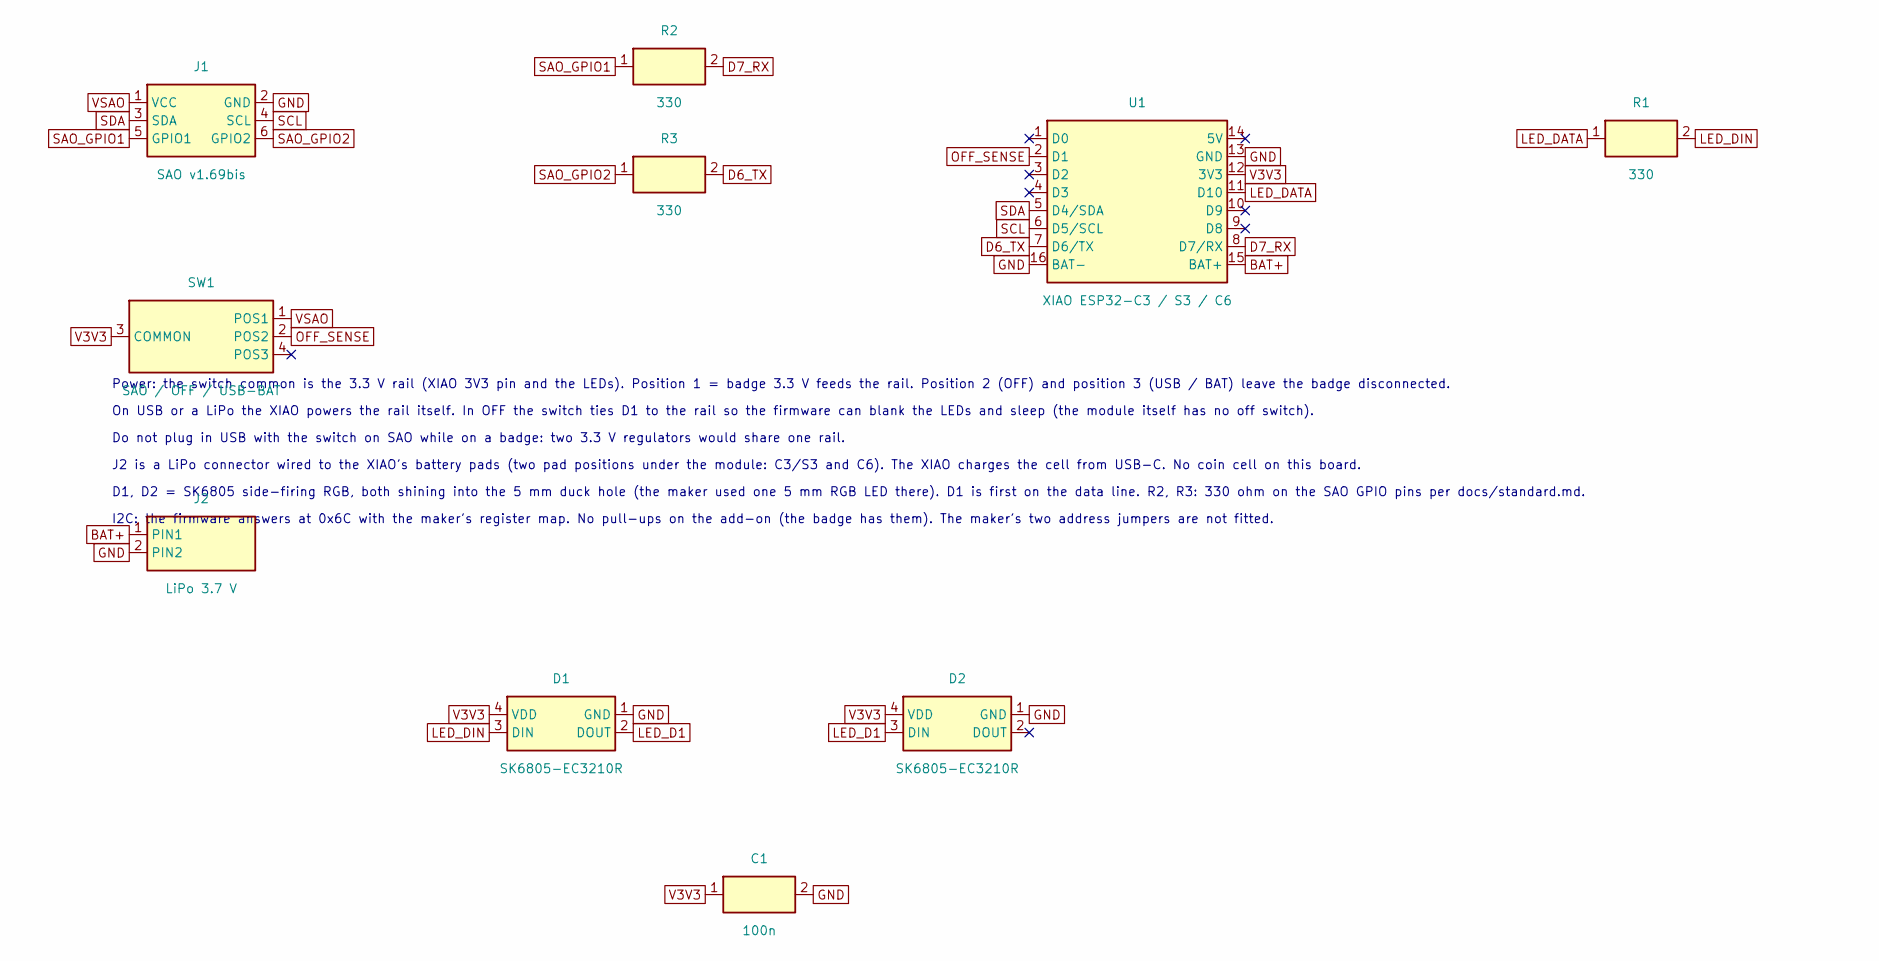
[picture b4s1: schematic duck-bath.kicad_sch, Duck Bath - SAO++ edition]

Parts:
C1: 100n; SAOPP_C_0603_1608Metric; MPN CC0603KRX7R9BB104; LCSC C14663
D1, D2: SK6805-EC3210R; SAOPP_LED-20_SK6805-EC3210R_SideView_RGB; MPN SK6805-EC3210R; LCSC C5378735
J1: SAO v1.69bis; SAOPP_CONN-01_BoxHeader_2x03_P2.54mm_SMD_XFCN_BH254VS-6P; MPN BH254VS-6P; LCSC C492445
J2: LiPo 3.7 V; SAOPP_CONN-10_JST_PH_S2B-PH-SM4-TB_1x02_Horizontal; MPN S2B-PH-SM4-TB(LF)(SN); LCSC C295747
R1, R2, R3: 330; SAOPP_R_0603_1608Metric; MPN 0603WAF3300T5E; LCSC C23138
SW1: SAO / OFF / USB-BAT; SAOPP_SW-01_Slide_SP3T_CK_PCM13SMTR; MPN PCM13SMTR; LCSC C221842
U1: XIAO ESP32-C3 / S3 / C6; SAOPP_MCU-01_Seeed_XIAO_SMD_C3_S3_C6; MPN XIAO ESP32-C3 / S3 / C6

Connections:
BAT+: J2.1 (PIN1), U1.15 (BAT+)
D6_TX: R3.2, U1.7 (D6/TX)
D7_RX: R2.2, U1.8 (D7/RX)
GND: C1.2, D1.1 (GND), D2.1 (GND), J1.2 (GND), J2.2 (PIN2), U1.13 (GND), U1.16 (BAT-)
LED_D1: D1.2 (DOUT), D2.3 (DIN)
LED_DATA: R1.1, U1.11 (D10)
LED_DIN: D1.3 (DIN), R1.2
OFF_SENSE: SW1.2 (POS2), U1.2 (D1)
SAO_GPIO1: J1.5 (GPIO1), R2.1
SAO_GPIO2: J1.6 (GPIO2), R3.1
SCL: J1.4 (SCL), U1.6 (D5/SCL)
SDA: J1.3 (SDA), U1.5 (D4/SDA)
V3V3: C1.1, D1.4 (VDD), D2.4 (VDD), SW1.3 (COMMON), U1.12 (3V3)
VSAO: J1.1 (VCC), SW1.1 (POS1)

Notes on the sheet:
Power: the switch common is the 3.3 V rail (XIAO 3V3 pin and the LEDs). Position 1 = badge 3.3 V feeds the rail. Position 2 (OFF) and position 3 (USB / BAT) leave the badge disconnected.
On USB or a LiPo the XIAO powers the rail itself. In OFF the switch ties D1 to the rail so the firmware can blank the LEDs and sleep (the module itself has no off switch).
Do not plug in USB with the switch on SAO while on a badge: two 3.3 V regulators would share one rail.
J2 is a LiPo connector wired to the XIAO's battery pads (two pad positions under the module: C3/S3 and C6). The XIAO charges the cell from USB-C. No coin cell on this board.
D1, D2 = SK6805 side-firing RGB, both shining into the 5 mm duck hole (the maker used one 5 mm RGB LED there). D1 is first on the data line. R2, R3: 330 ohm on the SAO GPIO pins per docs/standard.md.
I2C: the firmware answers at 0x6C with the maker's register map. No pull-ups on the add-on (the badge has them). The maker's two address jumpers are not fitted.

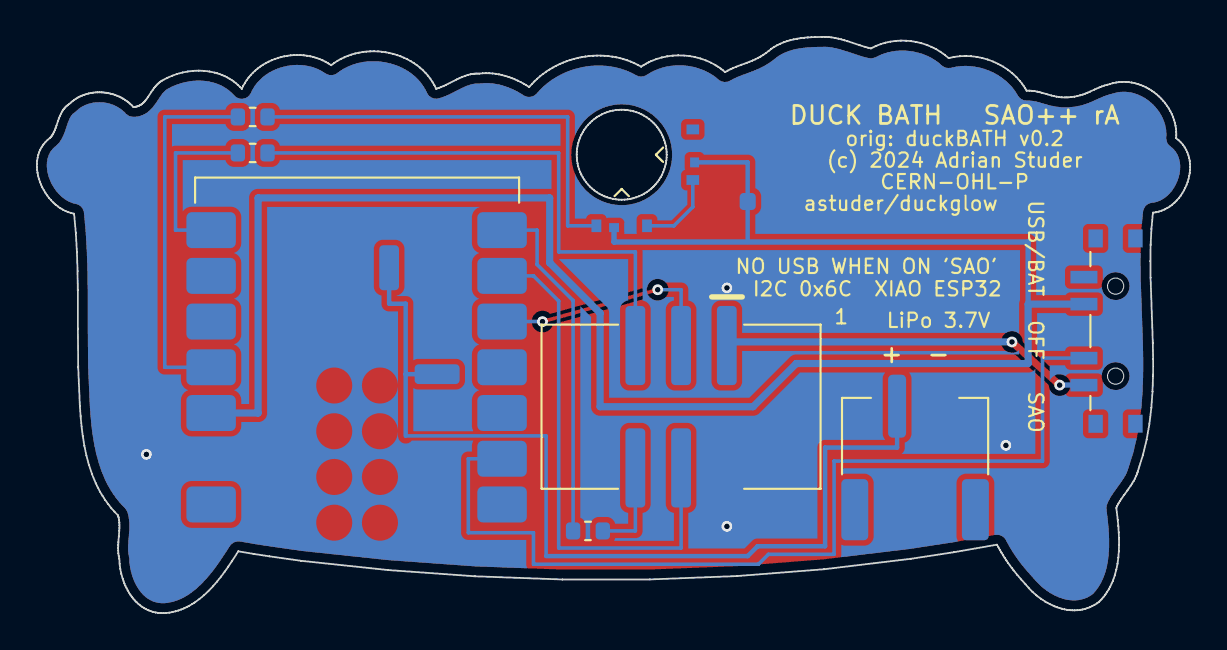
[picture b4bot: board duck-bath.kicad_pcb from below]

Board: 2 copper layers, 64.1 x 32.0 mm, 10 parts (10 on the bottom side), 14 nets.

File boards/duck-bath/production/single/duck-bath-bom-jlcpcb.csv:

Comment,Designator,Footprint,LCSC Part #
100n,C1,SAOPP_C_0603_1608Metric,C14663
SK6805-EC3210R,"D1,D2",SAOPP_LED-20_SK6805-EC3210R_SideView_RGB,C5378735
SAO v1.69bis,J1,SAOPP_CONN-01_BoxHeader_2x03_P2.54mm_SMD_XFCN_BH254VS-6P,C492445
LiPo 3.7 V,J2,SAOPP_CONN-10_JST_PH_S2B-PH-SM4-TB_1x02_Horizontal,C295747
330,"R1,R2,R3",SAOPP_R_0603_1608Metric,C23138
SAO / OFF / USB-BAT,SW1,SAOPP_SW-01_Slide_SP3T_CK_PCM13SMTR,C221842
XIAO ESP32-C3 / S3 / C6,U1,SAOPP_MCU-01_Seeed_XIAO_SMD_C3_S3_C6,

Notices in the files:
boards/duck-bath/hardware/duck-bath.kicad_pcb:
Original design: duckGLOW / duckBATH v0.2, (c) 2024 Adrian Studer (astuder), CERN-OHL-P, github.com/astuder/duckglow
boards/nsec-bomb/hardware/nsec-bomb.kicad_pcb:
Circuit: NorthSec badge team, Sao_Bomb (NorthSec 2025), github.com/nsec/nsec-badge, MIT licence. Outline and art: SAO++
boards/sao-jack/hardware/sao-jack.kicad_pcb:
Original design: hamster, DEF CON 30 SAO Jack 1.0 (2022), MIT license, github.com/hamster/defcon30
